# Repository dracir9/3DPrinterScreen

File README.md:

# 3D Printer Screen
3D Printer Screen is a 3d printer controller project based arround ESP32. The purpose of this project is to add wireless connectivity to the printer and simplify its operation through LCD and touchscreen interfaces.

**_Early development_**

## Hardware Prerequisites
This code is now targeted for use in a custom designed board which has an ESP32-S3 microcontroller, USB interface, micro SD card slot and 40-pin LCD connector. The design files in KiCad can be found .

Follow  if you want to build your own board or need a pinout reference.

Pay attention to these components requirements for the project to work:
- TFT LCD display compatible with [TFT_eSPI](https://github.com/Bodmer/TFT_eSPI) library. The current version of the sowftware uses an 8-bit parallel bus but SPI can also be used to control the LCD.
- ESP32-S3 Wroom-1 with at least 8MB of SPIRAM (ESP32-S3 Wroom-2 can also be used)
- EFM8BB10F8G microcontroller

## Current features
 - [x] SD card browser
 - [x] SD card printing
 - [x] Gcode preview
 
## Screenshots
#### Main screen

#### SD card browser

#### Gcode preview
 Based on [this design](https://www.thingiverse.com/thing:2508515)
 Based on [this design](https://www.thingiverse.com/thing:2914080)
 Based on [this design](https://www.thingiverse.com/thing:826836)
 Based on [this design](https://www.thingiverse.com/thing:1657791)
 
## Planned features
 - [ ] Movement, temperature, settings, file selection, etc. menus
 - [ ] SD card printing
 - [ ] WiFi printing

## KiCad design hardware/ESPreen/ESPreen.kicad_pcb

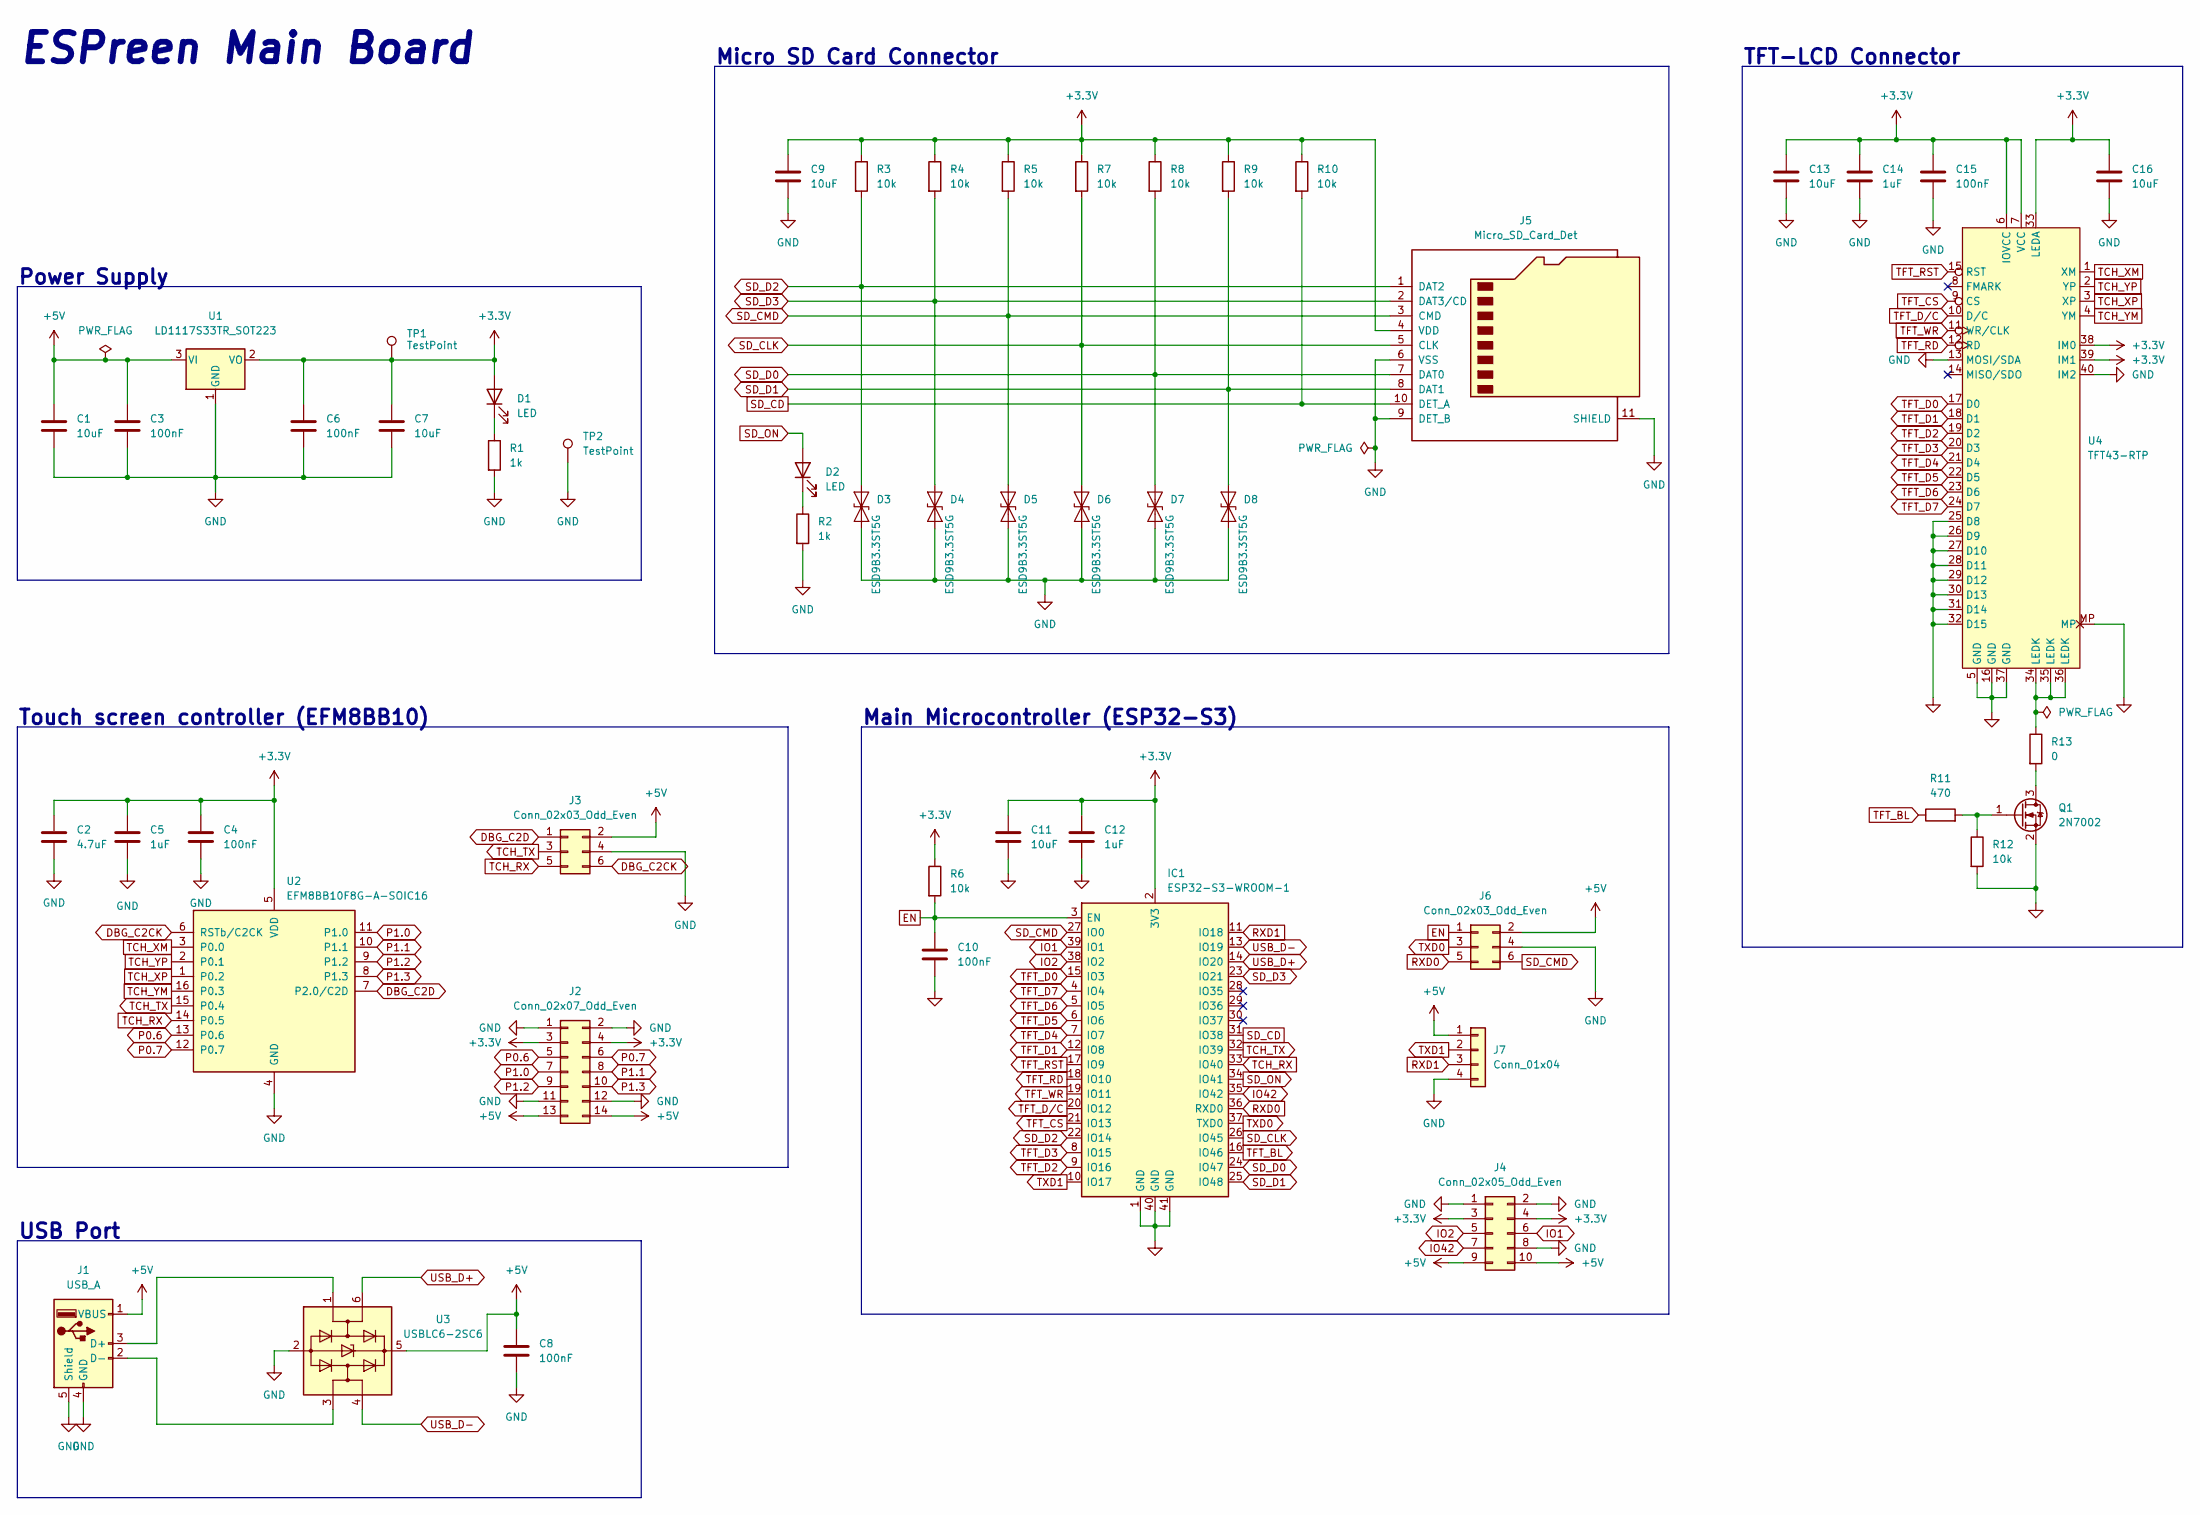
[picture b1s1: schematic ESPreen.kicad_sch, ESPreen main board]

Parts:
C1, C7, C9, C11, C13, C16: 10uF; C_0603_1608Metric_Pad1.08x0.95mm_HandSolder
C2: 4.7uF; C_0603_1608Metric_Pad1.08x0.95mm_HandSolder
C3, C4, C6, C8, C10, C15: 100nF; C_0603_1608Metric_Pad1.08x0.95mm_HandSolder
C5, C12, C14: 1uF; C_0603_1608Metric_Pad1.08x0.95mm_HandSolder
D1, D2: LED; LED_0603_1608Metric_Pad1.05x0.95mm_HandSolder
D3, D4, D5, D6, D7, D8: ESD9B3.3ST5G; D_SOD-523
IC1: ESP32-S3-WROOM-1; Manufacturer_Part_Number ESP32-S3-WROOM-1; Mouser Part Number 356-EP32S3WROOM1
J1: USB_A; USB_A_Molex_67643_Horizontal
J2: Conn_02x07_Odd_Even; PinHeader_2x07_P2.54mm_Vertical
J3, J6: Conn_02x03_Odd_Even; PinHeader_2x03_P1.27mm_Vertical_Shrouded
J4: Conn_02x05_Odd_Even; PinHeader_2x05_P2.54mm_Vertical
J5: Micro_SD_Card_Det; microSD_XunPu-F115
J7: Conn_01x04; Molex_SL_70553-0004_1x04_P2.54mm_Horizontal
Q1: 2N7002; SOT-23
R1, R2: 1k; R_0603_1608Metric_Pad0.98x0.95mm_HandSolder
R3, R4, R5, R6, R7, R8, R9, R10, R12: 10k; R_0603_1608Metric_Pad0.98x0.95mm_HandSolder
R11: 470; R_0603_1608Metric_Pad0.98x0.95mm_HandSolder
R13: 0; R_0603_1608Metric_Pad0.98x0.95mm_HandSolder
TP1, TP2: TestPoint; TestPoint_Pad_D1.0mm
U1: LD1117S33TR_SOT223; SOT-223-3_TabPin2
U2: EFM8BB10F8G-A-SOIC16; SOIC-16_3.9x9.9mm_P1.27mm
U3: USBLC6-2SC6; SOT-23-6
U4: TFT43-RTP; Jushuo-AFC07-S40ECA-00_1x40-1MP_P0.50mm_Horizontal

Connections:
+3.3V: C2.1, C4.1, C5.1, C6.1, C7.1, C9.1, C11.1, C12.1, C13.1, C14.1, C15.1, C16.1, D1.2 (A), IC1.2 (3V3), J2.3, J2.4, J4.3, J4.4, J5.4 (VDD), R3.1, R4.1, R5.1, R6.1, R7.1, R8.1, R9.1, R10.1, TP1.1, U1.2 (VO), U2.5 (VDD), U4.6 (IOVCC), U4.7 (VCC), U4.33 (LEDA), U4.38 (IM0), U4.39 (IM1)
+5V: C1.1, C3.1, C8.1, J1.1 (VBUS), J2.13, J2.14, J3.2, J4.9, J4.10, J6.2, J7.1, U1.3 (VI), U3.5 (VBUS)
DBG_C2CK: J3.6, U2.6 (RSTb/C2CK)
DBG_C2D: J3.1, U2.7 (P2.0/C2D)
EN: C10.1, IC1.3 (EN), J6.1, R6.2
GND: C1.2, C2.2, C3.2, C4.2, C5.2, C6.2, C7.2, C8.2, C9.2, C10.2, C11.2, C12.2, C13.2, C14.2, C15.2, C16.2, D3.1 (A1), D4.1 (A1), D5.1 (A1), D6.1 (A1), D7.1 (A1), D8.1 (A1), IC1.1 (GND), IC1.40 (GND), IC1.41 (GND), J1.4 (GND), J1.5 (Shield), J2.1, J2.2, J2.11, J2.12, J3.4, J4.1, J4.2, J4.8, J5.6 (VSS), J5.9 (DET_B), J5.11 (SHIELD), J6.4, J7.4, Q1.2 (S), R1.2, R2.2, R12.2, TP2.1, U1.1 (GND), U2.4 (GND), U3.2 (GND), U4.5 (GND), U4.13 (MOSI/SDA), U4.16 (GND), U4.25 (D8), U4.26 (D9), U4.27 (D10), U4.28 (D11), U4.29 (D12), U4.30 (D13), U4.31 (D14), U4.32 (D15), U4.37 (GND), U4.40 (IM2), U4.MP
IO1: IC1.39 (IO1), J4.6
IO2: IC1.38 (IO2), J4.5
IO42: IC1.35 (IO42), J4.7
unnamed: D1.1 (K), R1.1
unnamed: D2.1 (K), R2.1
unnamed: J1.2 (D-), U3.3 (I/O2)
unnamed: J1.3 (D+), U3.1 (I/O1)
unnamed: Q1.1 (G), R11.2, R12.1
unnamed: Q1.3 (D), R13.2
unnamed: R13.1, U4.34 (LEDK), U4.35 (LEDK), U4.36 (LEDK)
P0.6: J2.5, U2.13 (P0.6)
P0.7: J2.6, U2.12 (P0.7)
P1.0: J2.7, U2.11 (P1.0)
P1.1: J2.8, U2.10 (P1.1)
P1.2: J2.9, U2.9 (P1.2)
P1.3: J2.10, U2.8 (P1.3)
RXD0: IC1.36 (RXD0), J6.5
RXD1: IC1.11 (IO18), J7.3
SD_CD: IC1.31 (IO38), J5.10 (DET_A), R10.2
SD_CLK: D6.2 (A2), IC1.26 (IO45), J5.5 (CLK), R7.2
SD_CMD: D5.2 (A2), IC1.27 (IO0), J5.3 (CMD), J6.6, R5.2
SD_D0: D7.2 (A2), IC1.24 (IO47), J5.7 (DAT0), R8.2
SD_D1: D8.2 (A2), IC1.25 (IO48), J5.8 (DAT1), R9.2
SD_D2: D3.2 (A2), IC1.22 (IO14), J5.1 (DAT2), R3.2
SD_D3: D4.2 (A2), IC1.23 (IO21), J5.2 (DAT3/CD), R4.2
SD_ON: D2.2 (A), IC1.34 (IO41)
TCH_RX: IC1.33 (IO40), J3.5, U2.14 (P0.5)
TCH_TX: IC1.32 (IO39), J3.3, U2.15 (P0.4)
TCH_XM: U2.3 (P0.0), U4.1 (XM)
TCH_XP: U2.1 (P0.2), U4.3 (XP)
TCH_YM: U2.16 (P0.3), U4.4 (YM)
TCH_YP: U2.2 (P0.1), U4.2 (YP)
TFT_BL: IC1.16 (IO46), R11.1
TFT_CS: IC1.21 (IO13), U4.9 (CS)
TFT_D0: IC1.15 (IO3), U4.17 (D0)
TFT_D1: IC1.12 (IO8), U4.18 (D1)
TFT_D2: IC1.9 (IO16), U4.19 (D2)
TFT_D3: IC1.8 (IO15), U4.20 (D3)
TFT_D4: IC1.7 (IO7), U4.21 (D4)
TFT_D5: IC1.6 (IO6), U4.22 (D5)
TFT_D6: IC1.5 (IO5), U4.23 (D6)
TFT_D7: IC1.4 (IO4), U4.24 (D7)
TFT_D/C: IC1.20 (IO12), U4.10 (D/C)
TFT_RD: IC1.18 (IO10), U4.12 (RD)
TFT_RST: IC1.17 (IO9), U4.15 (RST)
TFT_WR: IC1.19 (IO11), U4.11 (WR/CLK)
TXD0: IC1.37 (TXD0), J6.3
TXD1: IC1.10 (IO17), J7.2
USB_D+: IC1.14 (IO20), U3.6 (I/O1)
USB_D-: IC1.13 (IO19), U3.4 (I/O2)

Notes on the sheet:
TFT-LCD Connector
Touch screen controller (EFM8BB10)
ESPreen Main Board
Micro SD Card Connector
Main Microcontroller (ESP32-S3)
Power Supply
USB Port

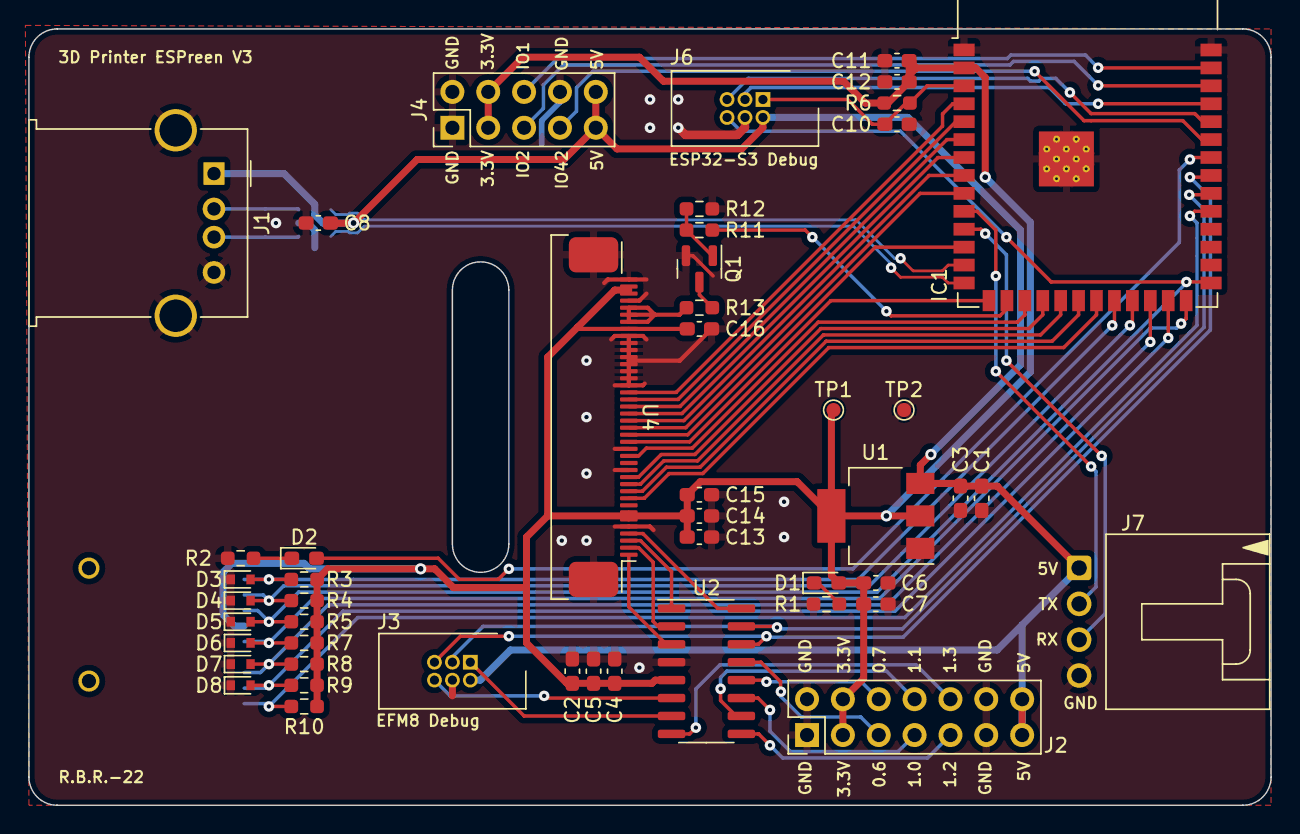
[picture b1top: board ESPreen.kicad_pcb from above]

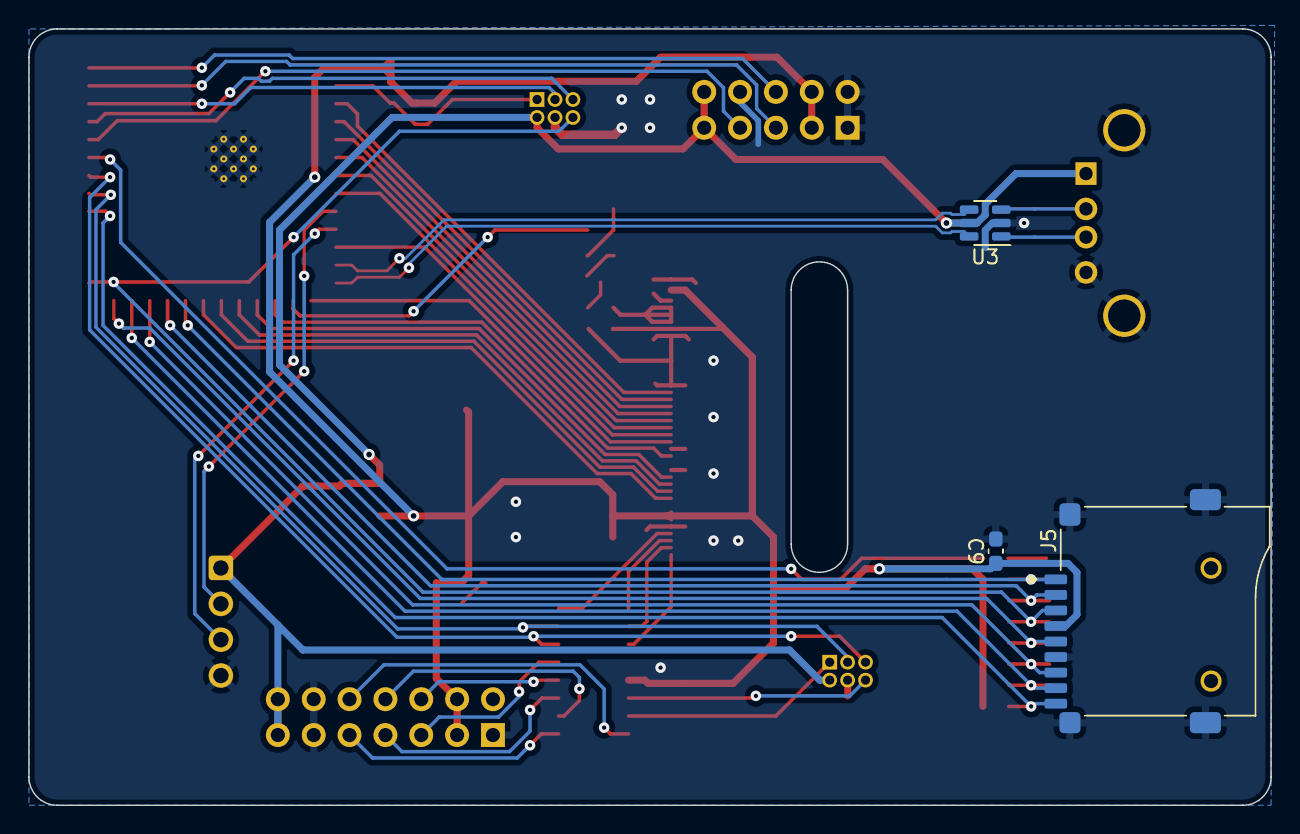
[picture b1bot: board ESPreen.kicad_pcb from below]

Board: 2 copper layers, 88.0 x 55.0 mm, 52 parts (3 on the bottom side), 56 nets.

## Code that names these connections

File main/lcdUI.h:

/**
 * @file   lcdUI.h
 * @author Ricard Bitriá Ribes (https://github.com/dracir9)
 * Created Date: 22-01-2022
 * -----
 * Last Modified: 26-08-2023
 * Modified By: Ricard Bitriá Ribes
 * -----
 * @copyright (c) 2022 Ricard Bitriá Ribes
 * 
 * This program is free software: you can redistribute it and/or modify
 * it under the terms of the GNU General Public License as published by
 * the Free Software Foundation, either version 3 of the License, or
 * (at your option) any later version.
 * 
 * This program is distributed in the hope that it will be useful,
 * but WITHOUT ANY WARRANTY; without even the implied warranty of
 * MERCHANTABILITY or FITNESS FOR A PARTICULAR PURPOSE.  See the
 * GNU General Public License for more details.
 * 
 * You should have received a copy of the GNU General Public License
 * along with this program.  If not, see <https://www.gnu.org/licenses/>.
 */

#ifndef LCD_UI_H
#define LCD_UI_H

#include <string>
#include <memory>
#include "driver/sdmmc_host.h"
#include "tftLCD.h"
#include "Screen.h"
#include "TchScr_Drv.h"
#include "printer.h"


/**
 * ADD NEW SCREEN
 *  1. Create source and header files under Menu folder
 *  2. Create new class named xxx_Scr that inherits Screen class publicly
 *  3. Override the update and render methods
 *  4. If necessary override the handleTouch method as well
 *  5. Include the new header in lcdUI.cpp
 *  6. Add screen name to ScreenType enum
 *  7. Add a new case in the updateObjects method in the lcdUI class
 */

class lcdUI
{
public:
    enum ScreenType : uint8_t
    {
        NONE,
        BLACK_SCR,
        INFO_SCR,
        MAIN_SCR,
        CONFIG_MENU_SCR,
        FILE_BROWSER_SRC,
        CONTROL_SCR,
        EXTRUDE_SCR,
        HEATERS_SCR,
        GCODE_PREVIEW_SCR,
        DISPLAY_CONF,
        PRINT_SCR,
        DRAW_SCR
    };

private:
    static lcdUI _instance;
    static bool init;
    
    static constexpr TchCalib calib = {
        .dx = 480,
        .rx_min = 900,
        .rx_max = 80,
        .dy = 320,
        .ry_min = 830,
        .ry_max = 100
    };

    tftLCD tft;
    tftSprite frame;
    std::unique_ptr<Screen> base;
    TchScr_Drv touchScreen;

    static constexpr gpio_num_t sd_cd_pin = GPIO_NUM_38;
    static constexpr gpio_num_t sd_led_pin = GPIO_NUM_41;
    static constexpr gpio_num_t sd_D0_pin = GPIO_NUM_47;
    static constexpr gpio_num_t sd_D1_pin = GPIO_NUM_48;
    static constexpr gpio_num_t sd_D2_pin = GPIO_NUM_14;
    static constexpr gpio_num_t sd_D3_pin = GPIO_NUM_21;
    static constexpr gpio_num_t sd_clk_pin = GPIO_NUM_45;
    static constexpr gpio_num_t sd_cmd_pin = GPIO_NUM_0;
    static constexpr gpio_num_t tch_tx_pin = GPIO_NUM_40;
    static constexpr gpio_num_t tch_rx_pin = GPIO_NUM_39;
    static constexpr gpio_num_t lcd_bl_pin = GPIO_NUM_46;

    bool booted = false;
    bool SDinit = false;

    static constexpr char mount_point[] = "/sdcard";
    sdmmc_card_t *card;

    xTaskHandle updateTaskH = nullptr;
    xTaskHandle touchTaskH = nullptr;
    xTaskHandle cardTaskH = nullptr;
    SemaphoreHandle_t touchMutex;

    ScreenType menuID = ScreenType::NONE;
    ScreenType newMenuID = ScreenType::BLACK_SCR;
    int64_t lastRender = 0;
    int64_t updateTime = 0;

    std::string selectedFile;
    
    lcdUI();
    ~lcdUI();

    static void updateTask(void* arg);
    static void touchTask(void* arg);
    static void cardDetectTask(void* arg);
    static void cardISRhandle(void* arg);

    bool initSD();
    void processTouch();
    esp_err_t updateDisplay();
    esp_err_t updateObjects();
public:

    static lcdUI* instance();
    esp_err_t begin();
    void setScreen(const ScreenType screen);
    void endSD();
    bool isSDinit() const;
    esp_err_t setFile(const std::string& file);
    const std::string& getFile() const { return selectedFile; }
    void clearFile() { selectedFile.clear(); }
    void requestUpdate();
    esp_err_t setBrightness(uint32_t duty);
    uint32_t getBrightness();
};

#endif

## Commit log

2019-07-02 getTxtBounds and getSize udate
    Overloaded get TextSize function to optimize for some use cases and fixed the vertical box getSize function
2019-07-03 Fixed and improved screen load/update
2019-07-05 Added max framerate and allowed text updates
    Cleaned up some code.
    Added debugging boxes arround widgets boundaries
2019-07-07 Add vector structure
2019-07-17 Added print with background
2019-07-17 Improved printBg efficiency
2019-07-19 Further improved drawCharBg speed
2019-07-19 Remove unnecessary files
2019-07-21 Switch to TFT_eSPI library
2019-07-23 Fixed new library compatibility issues
2019-07-23 Code cleanup
    - Removed old commented codes
    - Added some function descriptions
    - Improved sprite usage
2019-09-01 Split widgets
    Moved widget classes into its own header and source file to improve organization
2019-09-01 Converted veretical and horizontal box in templates
    verticalBox and horizontalBox are now tempates instead of dynamic arrays
2019-09-02 Created class for each menu screen
2019-09-09 Move menu classes into dedicated files
2019-11-07 Minor code corrections
    Improved code correctness and made small optimizations in some loops
2019-11-15 TouchScreen improvement
    Now we use registers to change pin states(it is faster)
2019-12-26 Updated Touch library
2020-10-01 Add utilities for debugging
2020-10-01 Change Serial.print to printf() function
2020-10-04 Update logging to ESP_LOG
2020-10-09 Add 3D vector class
2020-10-09 Add Machine class
2020-10-11 Added vector2 to vector.h file
2020-10-13 Add gcode parser
2020-10-13 Created Utils static class
2020-10-13 Rename canvas to Screen
2020-10-13 Changed lcdUI to be a standalone class
2020-10-13 Add file browser screen
2020-10-13 Add screen gcodePreview
2020-10-15 Add method to list SD content
2020-10-15 Fix linker complains
2020-10-15 Added functions to read and process gcode files
2020-10-22 Minor fix
2020-10-22 Improve Gcode reading speed
2020-10-22 Update README.md
    Change project name
2020-10-30 Switched render routine to a RTOS task
2020-11-01 Add touch panel routine and handle
2020-11-01 Add delayed menu update
2020-11-02 Extend SPI mutex and thread safety improvements
2020-11-04 Add SPIFFS icons
2020-11-04 Fix touch events registration
2020-11-04 Improve code style
2020-11-04 Implemented file browser core
2020-11-04 Add dedicated renderPage function
2020-11-04 Add visual debugging for touch input
2020-11-04 Add folder icon and update file icon
2020-11-28 Folders can be oppened
2020-12-13 Implemented file navigation bar
2020-12-15 Added icons and fixed rendering bug
2020-12-17 Change file name c strings to std:string
2020-12-17 Send selected file to preview screen
2020-12-20 Increase operation flexibility of Vector structure
2020-12-20 Reduce verbosity
2020-12-20 Add comment parsing and auto scale
2020-12-26 Code cleanup
2020-12-26 Created shorter names for common vector types
2020-12-26 Added Gcode 3D preview
2020-12-27 Created Vector float type specialization
2020-12-27 Variable FOV and simple lightning
2020-12-28 Report significant heap size changes
2020-12-28 Prevent watchdog from triggering
2020-12-29 Viewer optimizations
2020-12-30 Parse comments using fletcher16 checksum
2020-12-30 Revert "Parse comments using fletcher16 checksum"
    This reverts commit 8d7ccf24d766834dfe5a43bff61d8aeb2d4abad3.
2020-12-30 Minor bug fixes
2020-12-30 Add gcode icon
2021-01-01 Custom drawLine function with depth coordinate
2021-01-01 Functional z buffer
2021-01-02 Rendering optimizations and bugfixes
2021-01-02 Fixed code to prevent overflow
2021-01-03 Changed fps to minimum frame time
2021-01-03 Frame Time accessor
2021-01-03 Add destructor to GcodePreview_Scr class
2021-01-03 Moved initialization to dedicated function
2021-01-03 Non blocking Gcode rendering
2021-01-03 Add print information
2021-01-04 Clean old files
2021-01-04 Modify Screen base class
2021-01-04 Restore old screen prototype
2021-01-05 Update info screen to new API
2021-01-06 Add sd card button and code cleanup
2021-01-06 Add new icon
2021-01-06 Added two more icons
2021-01-06 Change screen style
2021-01-06 Add return icon
2021-01-07 Moved page arrows to the bottom
2021-01-07 Expanded folder header to fill screen
2021-01-07 Update folder name display
2021-01-07 Update Gcode preview style
2021-01-08 Fix rendering bug and raise TFT library version
2021-01-11 Disabled Adafruit fonts
2021-01-11 Make tft instance private
2021-01-11 Change drawing function to pas tft by reference
2021-01-11 Prevent tft instances from being copied
2021-01-11 Add utility to print screen to file through serial
2021-01-11 Moved screen server into utility files
2021-01-12 Utilities can now be enabled independently
2021-01-12 Fix screen refresh rate bug
2021-01-13 Minor updates
2021-01-14 Make selectedFile private
2021-01-14 Performance test
2021-01-15 Add draw string wrapped in a box function
2021-01-15 Show wrapped text for long filenames
2021-01-15 Add screenshots
2021-01-16 Gcode rendering worktime dependent on framerate
2021-01-16 Configurable heatbeds, extruder and fans number
2021-01-18 Add heatbed, extruder and fan icons
2021-01-18 Update screenshots
2021-01-18 Add one more screenshot
2021-01-18 Revert "Merge branch 'improved_file_read' into dev_branch"
    This reverts commit 55cdbc70ee8688abff8b8f381d6881529b796206, reversing
    changes made to 535a0b22a11378eef4235add4c4471a5f0ed58e0.
2021-03-11 Configure code for new board
2021-03-13 Change to float vectors
2021-03-13 Change Zbuffer to external RAM
2021-03-13 Remove old code
2021-03-15 Add rendering percentage
2021-03-16 Fix SPI management problem
2021-03-16 Implement SD card detect pin
2021-03-16 Read touch on interrupt
2021-03-28 Small updates
2022-01-21 Set buffers for file read
2022-01-21 Update gitignore
2022-01-21 Update license
2022-01-21 Switch to ESP-IDF
2022-01-21 Add Arduuino component
2022-01-21 Add remaining components
2022-01-22 Configure device
2022-01-22 Add previous code
2022-01-22 partial update touch driver and fix compile errors
2022-01-31 Minor cleanup
2022-01-31 Update touch driver
2022-01-31 Touch driver minor fix
2022-02-02 Reorganize and cleanup lcdUI
2022-02-02 Update Tch_drv calls
2022-02-02 Update screen on demand only
2022-02-06 Update touch driver: Fix get event deadlock
2022-02-06 Update function calls to handle new touch driver
2022-02-12 Implement buttons in file browser
2022-02-12 Update TFT driver
2022-02-12 Minor form changes
2022-02-13 Remove dbg_log
2022-02-13 Add dbg_log
2022-02-13 Add gcode renderer
2022-02-16 Switch to new render engine
2022-02-20 Fix render engine state issues
2022-02-26 Update log macros and improve error handling
2022-02-26 Fix write tmp bug
2022-02-26 Minor fix and documentation
2022-02-26 Optimize camera position calculation
2022-03-06 Add delete cache function
2022-03-06 Parse comments for information
2022-03-06 Fix rendering bugs
2022-03-06 Add print info, fix bugs and rename preview screen
2022-03-11 Remove old files
2022-03-11 Custom float parser for render time reduction
2022-03-11 Minor changes
2022-03-11 Add documentation and improve error checking
2022-03-12 Bug fix and improved camera orientation system
2022-03-12 Fix camera rotation
2022-03-12 Fix bugs and add more error checking
2022-03-13 Load image directly if possible
2022-03-14 Add print info to render cache Add cases to comment parser
2022-03-19 Permanent z buffer
2022-03-24 Handle render cancellation and restart
2022-03-24 Display render engine error
2022-03-26 Improve task sincronization and notifications
2022-03-26 Handle card extraction
2022-03-26 Simplify file information and better img checks
2022-03-26 Alternative filament lenght calculation
2022-04-09 Update to new board
2022-04-10 Add project configuration options to idf menu
2022-04-10 Update TFT_eSPI
2022-04-11 Update components
2022-04-11 Removed TFT_eSPI
2022-04-11 Add TFT_eSPI fork
2022-04-11 Update names
2022-04-11 Add harware schematic
2022-04-11 Rename document
2022-04-11 Fis README
2022-04-11 Fix name
2022-04-11 Rename for consistency
2022-04-11 Initial setup for configuration screen
2022-04-11 Add display configuration screen
2022-04-12 Update touch library and fix some bugs
2022-04-14 Fix info display bug
2022-04-14 Improve slider
2022-04-15 Setup display backlight PWM and control menu
2022-04-28 Update ESP-IDF and TFT_eSPI
2022-05-02 Add printer class and uart communication
2022-05-08 Add transmit task, event queue and ready flag
2022-05-21 Add TxEvent queue
2022-05-21 Fix TFT_eSPI issue
2022-06-01 Change compiler settings
2022-06-06 Separate serial data in lines
2022-06-06 Add counter to log
2022-06-09 Fix serial line separation and add parse options
2022-06-11 Fix parser issue
2022-06-11 Allocate dynamic extruder fields
2022-06-11 Parse temperatures
2022-06-11 Conver printer to singleton
2022-06-11 Display real temperatures
2022-06-12 Send gcode file to printer
2022-06-15 Parse and display position
2022-06-24 Create print screen
2022-06-24 Add Draw screen
2022-06-24 Add funtion to report state
2022-06-24 Handle printer state in preview_Scr
2022-06-24 Start printing on print_Scr
2022-11-26 Update submodules
2022-11-26 Add send feedrate command
2022-11-30 Create KiCad project
2023-01-26 Update to finished board
2023-02-20 Update PCB schematic
2023-02-20 Minor pcb update
2023-02-20 Switch to esp32s3
2023-02-20 Update touch driver library
2023-02-25 Update tft eSPI
2023-02-25 Update SD card pins
2023-02-25 Update printer UART port and pins
2023-02-25 Centralize pin assignments
2023-02-25 Update partition table
2023-02-25 Stop booting on certain reset reasons
2023-02-25 Rename files
2023-02-25 Rename again with lower case
2023-02-25 Change to early log
2023-02-26 Disable warnings in TFT_eSPI
2023-02-26 Disable warnings in TchScr_Drv
2023-02-26 Update SD card driver with new pins
2023-02-26 Supress warnings
2023-02-26 Remove const qualifier
2023-02-26 Default initialize structs
2023-02-26 Enable long file names
2023-02-27 Increase worker stack. Improve memory checks.
2023-02-27 Sync with upstream TFT_eSPI
2023-03-04 Remove generated files
2023-03-04 Add component manager files
2023-03-05 Remove UART Tx Task
2023-03-10 Rework code for sending commands
2023-03-10 Switch to std::vector for easier memory management
2023-03-11 Remove warning
2023-03-11 Update c++ standard
2023-03-11 Switch to managed pointers
2023-03-11 Add heap information logging
2023-03-11 Switch to managed fstream
2023-04-10 Code style update and documentation
2023-04-10 Add control screen
2023-04-16 Add touch buttons and UI layout update
2023-04-16 Add button text. Fix button glitches
2023-04-18 Implement toolhead movement
2023-04-19 Add step controls
2023-05-31 Update libraries and ESP-IDF
2023-06-03 Rename variables
2023-06-03 Update KiCad version
2023-06-03 Update Vector library
2023-06-10 Reorganize move screen
2023-07-19 Update kicad files
2023-07-24 Display four bottom buttons
2023-08-02 Add extruder control screen
2023-08-08 Add icons to bottom buttons
2023-08-10 Add position display and more homing options
2023-08-10 Add homing buttons
2023-08-10 Add function to home printer axes
2023-08-10 Send home cmd to printer
2023-08-10 Update libraries
2023-08-10 Simplify senCommand function
2023-08-12 Adjust extruder screen layout
2023-08-12 Add function to move extruder
2023-08-12 Add tool number option
2023-08-12 Implement extruder screen logic
2023-08-12 Add temperature display
2023-08-12 Update header
2023-08-12 Add new heater screen
2023-08-12 Integrate heater screen with other screens
2023-08-12 Adjust element spacing
2023-08-13 Add functions to set the temperature
2023-08-13 Adjust heater screen layout and logic
2023-08-24 Remove the need for a sprite in tftLCD
2023-08-26 Remove unused functions from tftLCD
2023-08-30 Add full screen frame buffer
2023-08-30 Add case in printer serial parser
